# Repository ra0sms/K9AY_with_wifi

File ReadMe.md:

# K9AY receiving loop with Wi-Fi control

A remote switch for the K9AY receiving loop antenna. It is controlled over Wi-Fi from any web browser on a phone, tablet or PC. You can also control it from scripts and logging software through a simple HTTP API.

## Features

* **8 directions**: two loops switched by relays (N, NE, E, SE, S, SW, W, NW)
* **Switchable termination resistor (Rload)**: 300, 390, 430, 470, 510 or 560 Ohm
* **Built-in preamplifier**: +15 dB, switched on and off from the web page
* **ESP8266** controller (ESP-12 module with external Wi-Fi antenna)
* **Wi-Fi access point and client at the same time**: connect directly to the box, or through your home Wi-Fi network
* **Single power supply**: 12–13.8 V DC
* **Remembers its state**: direction, Rload and preamp are restored after a power loss
* **Custom direction names**: e.g. azimuth, "EU", "JA"
* **HTTP/JSON API** for automation
* Open hardware (KiCad) and open source firmware (Arduino IDE)

More information about the loop and construction details: https://ra0sms.com/k9ay-wifi-interface/

## Hardware

| Parameter | Value |
|---|---|
| Supply voltage | 12–13.8 V DC (power supply rated at least 500 mA) |
| Current consumption | about 250 mA |
| Loop connection | screw terminals **N S E W** |
| Radials / ground | screw terminal **GROUND** |
| Wi-Fi range | up to 50 m with an entry-level router |
| Case | 170 × 120 × 55 mm, ABS, IP68, cable glands for 3–7 mm cable |

* [Latest schematic (PDF)](KiCad/K9AY_switch/K9AY_switch.pdf)
* KiCad project, Gerbers and interactive BOM: [KiCad/K9AY_switch](KiCad/K9AY_switch/)

## Quick start

1. Power on the box. It creates a Wi-Fi access point:
   * Network name: **`K9AY_Loop_XXXXXX`**, where `XXXXXX` is the unique chip ID of the controller (it is also printed to the serial port at startup)
   * Password: **`1234567890`**
2. Connect your phone or PC to this network. Most devices open the controller page automatically (captive portal). If yours does not, open **http://192.168.4.1** in a browser.
3. To use the box through your home network, open **WiFi Configuration**. Pick your network from the list (click a row to fill in the name), enter the password and press **Connect**. Your router must have DHCP enabled.
4. Once it is connected, the green LED is on and the WLAN IP address is shown on the WiFi page. From any device in your home network, open the controller at:
   * **http://k9ay.local** (mDNS: Windows 10+, macOS, iOS, Linux; Android support depends on the browser), or
   * the IP address shown on the WiFi page (it can also be found in the router's DHCP list).

By default the access point stays on all the time, so you can always reach the box at `192.168.4.1`, even if the home network is down. It can also be disabled while the box is connected to your home network (see below).

## Web interface

| Page | Address | Description |
|---|---|---|
| Home | `/` | Connection info, uptime, firmware version, links to other pages |
| Direction Control | `/switch` | Main control page |
| WiFi Configuration | `/wifi` | Access point and WLAN status, network scan, connect to a router |
| Direction Labels | `/labels` | Rename the direction buttons |

### Direction Control

* The direction buttons are laid out as a compass rose. The selected direction is highlighted and also shown in the centre.
* **Rload**: selects the termination resistor of the loop.
* **PREAMP ON / OFF**: switches the +15 dB preamplifier.
* **TURN ALL OFF**: releases all relays, disconnects Rload and switches off the preamp.
* The status line at the top shows the current state, e.g. `NE 470 Ohm +15dB`. The page refreshes every 2 seconds, so changes made from another device or through the API appear by themselves. If the controller cannot be reached, the status line turns red.

### WiFi Configuration

* Name, status and IP address of the built-in access point
* **Disable access point while connected to WLAN**: the access point is turned off 30 seconds after the box connects to your home network. It turns back on automatically if the saved network is unavailable for 15 seconds, and it is always on after power-on until the WLAN connection is up. If you lose access, simply power-cycle the box and connect to `K9AY_Loop_XXXXXX`.
* Saved WLAN network, connection status, IP address, signal level and connection time
* List of available networks, sorted by signal level (press **Scan** to refresh)
* To make the box forget the saved network, submit the form with an empty SSID
* SSID up to 32 characters, password up to 64 characters

If the router cannot be reached (wrong password, router off), the controller retries every 60 seconds. The access point is active in the meantime.

### Direction Labels

Each of the 8 directions can be given its own name, up to 23 bytes. Cyrillic and other UTF-8 characters are supported. An empty field restores the default name. **Reset to defaults** restores all names at once.

## LED

| LED | Meaning |
|---|---|
| On | Connected to the home Wi-Fi network |
| Off | Not connected to WLAN (access point only) |

## HTTP API

The box can be controlled from scripts, logging software or home automation.

**Read state**

```
GET /api/state
```
```json
{"dir":1,"r":470,"pa":true,"labels":["N","NE","E","SE","S","SW","W","NW"]}
```

* `dir`: index into `labels` (0 = N, 1 = NE … 7 = NW), `-1` means off
* `r`: Rload in Ohm, `0` means off
* `pa`: preamp state

**Change state** (`POST`, form-encoded; parameters can be combined)

| Parameter | Values |
|---|---|
| `dir` | `N`, `NE`, `E`, `SE`, `S`, `SW`, `W`, `NW` |
| `r` | `300`, `390`, `430`, `470`, `510`, `560` |
| `pa` | `1` = on, `0` = off |
| `off` | `1` = turn everything off |

The response is the new state in the same format as `/api/state`. An invalid value returns HTTP 400.

```sh
curl -d "dir=NE&r=470&pa=1" http://k9ay.local/set
curl -d "off=1" http://k9ay.local/set
curl http://k9ay.local/api/state
```

**Other endpoints**

* `GET /api/info`: network status and uptime
* `GET /api/scan`: Wi-Fi scan results (`{"scanning":true}` while the scan is running)

## Firmware

Source: [src/Arduino/sketch_k9ay/sketch_k9ay.ino](src/Arduino/sketch_k9ay/sketch_k9ay.ino)

### Building

1. Install the [ESP8266 Arduino core](https://github.com/esp8266/Arduino) (tested with 3.1.2). No extra libraries are needed.
2. Board: **Generic ESP8266 Module**, Flash Size **4MB**.
3. Upload through a USB-UART adapter (GPIO0 to GND while resetting).

### Settings in the source code

At the top of the sketch:

| Constant | Default | Description |
|---|---|---|
| `softAP_password` | `1234567890` | Access point password (at least 8 characters) |
| `myHostname` | `k9ay` | mDNS name (`http://k9ay.local`) |
| `www_user` / `www_pass` | empty | Login for the web interface and API. If `www_user` is empty, no login is required |

### Stored data

The settings are stored in the emulated EEPROM, starting at address 128: Wi-Fi credentials, direction labels and the current switch state. The state is written 30 seconds after the last change, and only if it differs from the saved one. This keeps flash wear low. On the first start after an update from the old firmware, the Wi-Fi credentials saved by the old version are moved over automatically.

### Pinout

| ESP8266 | Function |
|---|---|
| GPIO13 / GPIO14 | 74HC595 data / clock (HSPI) |
| GPIO15 | 74HC595 latch |
| GPIO12 | 74HC595 output enable |
| GPIO4 | Preamp on/off |
| GPIO5 | Status LED |

Two chained 74HC595 shift registers drive the relays. The first one drives Rload (bits 0–5), the second one the direction relays.

## Documentation

* [Manual (EN)](docs/Manual_K9AY_en.pdf)
* [Manual (RU)](docs/Manual_K9AY_ru.pdf)

## License

MIT, see [LICENSE](LICENSE). © 2022 Anton Gavrilov RA0SMS

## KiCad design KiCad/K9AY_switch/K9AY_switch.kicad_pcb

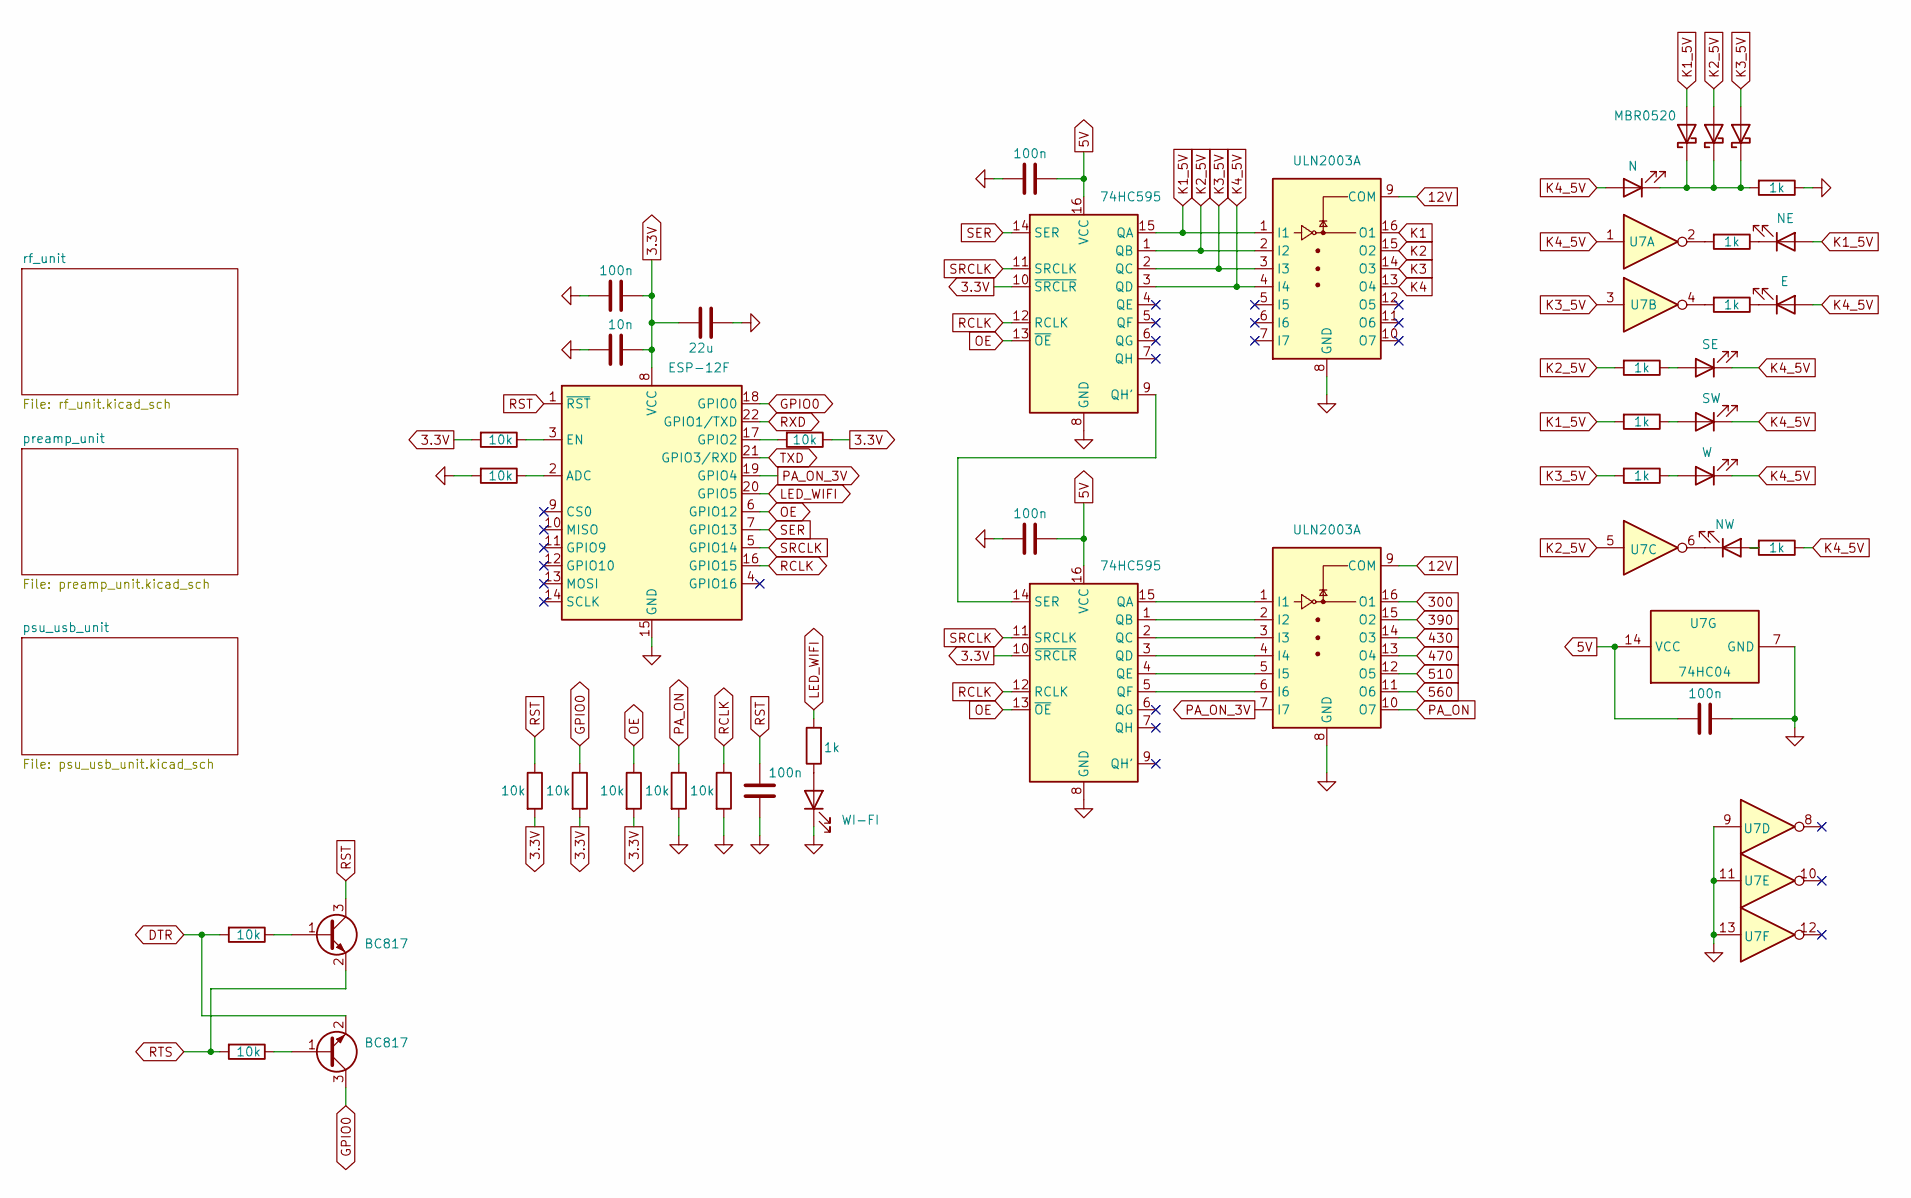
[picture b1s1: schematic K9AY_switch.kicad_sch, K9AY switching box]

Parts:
C6, C16, C17, C18, C19: 100n; C_1206_3216Metric
C14: 10n; C_1206_3216Metric
C15: 22u; C_1206_3216Metric
D4: WI-FI; LED_1206_3216Metric
D5: N; LED_1206_3216Metric
D6, D7, D8: MBR0520; D_SOD-123
D9: NE; LED_1206_3216Metric
D10: E; LED_1206_3216Metric
D11: SE; LED_1206_3216Metric
D12: SW; LED_1206_3216Metric
D13: W; LED_1206_3216Metric
D14: NW; LED_1206_3216Metric
Q2, Q3: BC817; SOT-23
R7, R12, R13, R14, R15, R16, R17, R18, R20, R21: 10k; R_1206_3216Metric
R19, R22, R23, R24, R25, R26, R27, R28: 1k; R_1206_3216Metric
U1: ESP-12F; ESP-12E
U2, U3: 74HC595; SOIC-16_3.9x9.9mm_P1.27mm
U4, U8: ULN2003A; SOIC-16_3.9x9.9mm_P1.27mm
U7: 74HC04; SOIC-14_3.9x8.7mm_P1.27mm

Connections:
3.3V: C6.2, C14.2, C15.2, R12.2, R14.2, R15.2, R16.1, R20.2, U1.8 (VCC), U2.10 (~SRCLR), U3.10 (~SRCLR); also elsewhere on the board
5V: C17.2, C18.2, C19.1, U2.16 (VCC), U3.16 (VCC), U7.14 (VCC); also elsewhere on the board
12V: U4.9 (COM), U8.9 (COM); also elsewhere on the board
300: U8.16 (O1); also elsewhere on the board
390: U8.15 (O2); also elsewhere on the board
430: U8.14 (O3); also elsewhere on the board
470: U8.13 (O4); also elsewhere on the board
510: U8.12 (O5); also elsewhere on the board
560: U8.11 (O6); also elsewhere on the board
DTR: Q3.2 (E), R18.2; also elsewhere on the board
GND: C6.1, C14.1, C15.1, C16.1, C17.1, C18.1, C19.2, D4.1 (K), R7.2, R13.2, R21.2, R22.1, U1.15 (GND), U2.8 (GND), U3.8 (GND), U4.8 (GND), U7.7 (GND), U7.9, U7.11, U7.13, U8.8 (GND); also elsewhere on the board
GPIO0: Q3.3 (C), R15.1, U1.18 (GPIO0)
K1: U4.16 (O1); also elsewhere on the board
K1_5V: D6.2 (A), D9.2 (A), R26.2, U2.15 (QA), U4.1 (I1)
K2: U4.15 (O2); also elsewhere on the board
K2_5V: D7.2 (A), R25.2, U2.1 (QB), U4.2 (I2), U7.5
K3: U4.14 (O3); also elsewhere on the board
K3_5V: D8.2 (A), R27.2, U2.2 (QC), U4.3 (I3), U7.3
K4: U4.13 (O4); also elsewhere on the board
K4_5V: D5.2 (A), D10.2 (A), D11.1 (K), D12.1 (K), D13.1 (K), R28.1, U2.3 (QD), U4.4 (I4), U7.1
LED_WIFI: R19.2, U1.20 (GPIO5)
unnamed: D4.2 (A), R19.1
unnamed: D5.1 (K), D6.1 (K), D7.1 (K), D8.1 (K), R22.2
unnamed: D9.1 (K), R23.1
unnamed: D10.1 (K), R24.1
unnamed: D11.2 (A), R25.1
unnamed: D12.2 (A), R26.1
unnamed: D13.2 (A), R27.1
unnamed: D14.2 (A), R28.2
unnamed: D14.1 (K), U7.6
unnamed: Q2.1 (B), R18.1
unnamed: Q3.1 (B), R17.1
unnamed: R23.2, U7.2
unnamed: R24.2, U7.4
unnamed: R13.1, U1.2 (ADC)
unnamed: R12.1, U1.3 (EN)
unnamed: R16.2, U1.17 (GPIO2)
unnamed: U2.9 (QH'), U3.14 (SER)
unnamed: U3.15 (QA), U8.1 (I1)
unnamed: U3.1 (QB), U8.2 (I2)
unnamed: U3.2 (QC), U8.3 (I3)
unnamed: U3.3 (QD), U8.4 (I4)
unnamed: U3.4 (QE), U8.5 (I5)
unnamed: U3.5 (QF), U8.6 (I6)
OE: R20.1, U1.6 (GPIO12), U2.13 (~OE), U3.13 (~OE)
PA_ON: R21.1, U8.10 (O7); also elsewhere on the board
PA_ON_3V: U1.19 (GPIO4), U8.7 (I7)
RCLK: R7.1, U1.16 (GPIO15), U2.12 (RCLK), U3.12 (RCLK)
RST: C16.2, Q2.3 (C), R14.1, U1.1 (~RST)
RTS: Q2.2 (E), R17.2; also elsewhere on the board
RXD: U1.22 (GPIO1/TXD); also elsewhere on the board
SER: U1.7 (GPIO13), U2.14 (SER)
SRCLK: U1.5 (GPIO14), U2.11 (SRCLK), U3.11 (SRCLK)
TXD: U1.21 (GPIO3/RXD); also elsewhere on the board

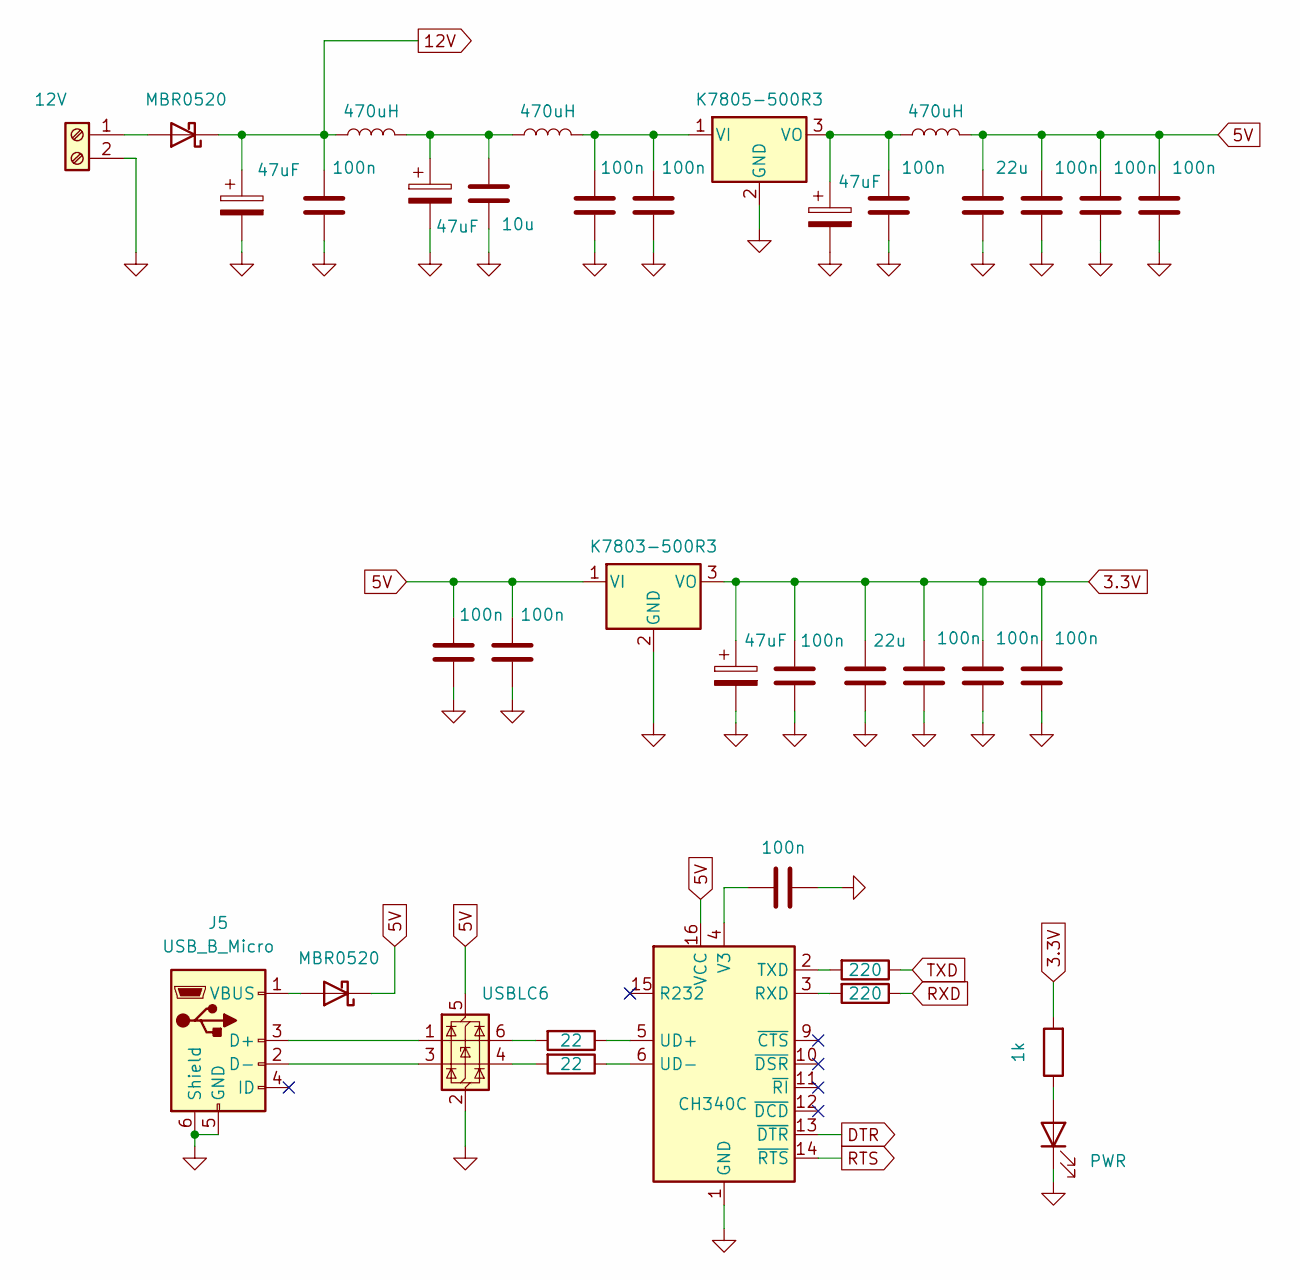
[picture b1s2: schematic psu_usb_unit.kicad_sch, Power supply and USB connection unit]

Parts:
C1, C7, C10, C30: 47uF; CP_Radial_D5.0mm_P2.50mm
C2, C8, C11, C13, C22, C23, C24, C25, C26, C27, C28, C29, C35, C36: 100n; C_1206_3216Metric
C9, C12: 22u; C_1206_3216Metric
C32: 10u; C_1206_3216Metric
D1, D3: MBR0520; D_SOD-123
D2: PWR; LED_1206_3216Metric
J4: 12V; TerminalBlock_MetzConnect_Type011_RT05502HBWC_1x02_P5.00mm_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
J5: USB_B_Micro; USB_Mini-B_Wuerth_65100516121_Horizontal
L2, L3, L4: 470uH; L_Radial_D10.0mm_P5.00mm_Neosid_SD12_style3
R1: 1k; R_1206_3216Metric
R8, R9: 22; R_1206_3216Metric
R10, R11: 220; R_1206_3216Metric
U5: K7803-500R3; TO-220-3_Vertical
U6: K7805-500R3; TO-220-3_Vertical
U11: CH340C; SOIC-16_3.9x9.9mm_P1.27mm
U12: USBLC6; SOT-23-6

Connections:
3.3V: C7.1, C8.1, C9.1, C27.1, C28.1, C29.1, R1.2, U5.3 (VO); also elsewhere on the board
5V: C12.1, C24.1, C25.1, C26.1, C35.1, C36.1, D3.1 (K), L4.2, U5.1 (VI), U11.16 (VCC), U12.5 (VBUS); also elsewhere on the board
12V: C1.1, C2.1, D1.1 (K), L3.1; also elsewhere on the board
DTR: U11.13 (~DTR); also elsewhere on the board
GND: C1.2, C2.2, C7.2, C8.2, C9.2, C10.2, C11.2, C12.2, C13.2, C22.2, C23.2, C24.2, C25.2, C26.2, C27.2, C28.2, C29.2, C30.2, C32.2, C35.2, C36.2, D2.1 (K), J4.2, J5.5 (GND), J5.6 (Shield), U5.2 (GND), U6.2 (GND), U11.1 (GND), U12.2 (GND); also elsewhere on the board
unnamed: C30.1, C32.1, L2.1, L3.2
unnamed: D1.2 (A), J4.1
unnamed: D2.2 (A), R1.1
unnamed: D3.2 (A), J5.1 (VBUS)
unnamed: J5.3 (D+), U12.1 (I/O1)
unnamed: J5.2 (D-), U12.3 (I/O2)
unnamed: R8.2, U12.4 (I/O2)
unnamed: R9.2, U12.6 (I/O1)
unnamed: C22.1, C23.1, L2.2, U6.1 (VI)
unnamed: C10.1, C11.1, L4.1, U6.3 (VO)
unnamed: R11.2, U11.3 (RXD)
unnamed: R10.2, U11.2 (TXD)
unnamed: R9.1, U11.5 (UD+)
unnamed: R8.1, U11.6 (UD-)
unnamed: C13.1, U11.4 (V3)
RTS: U11.14 (~RTS); also elsewhere on the board
RXD: R11.1; also elsewhere on the board
TXD: R10.1; also elsewhere on the board

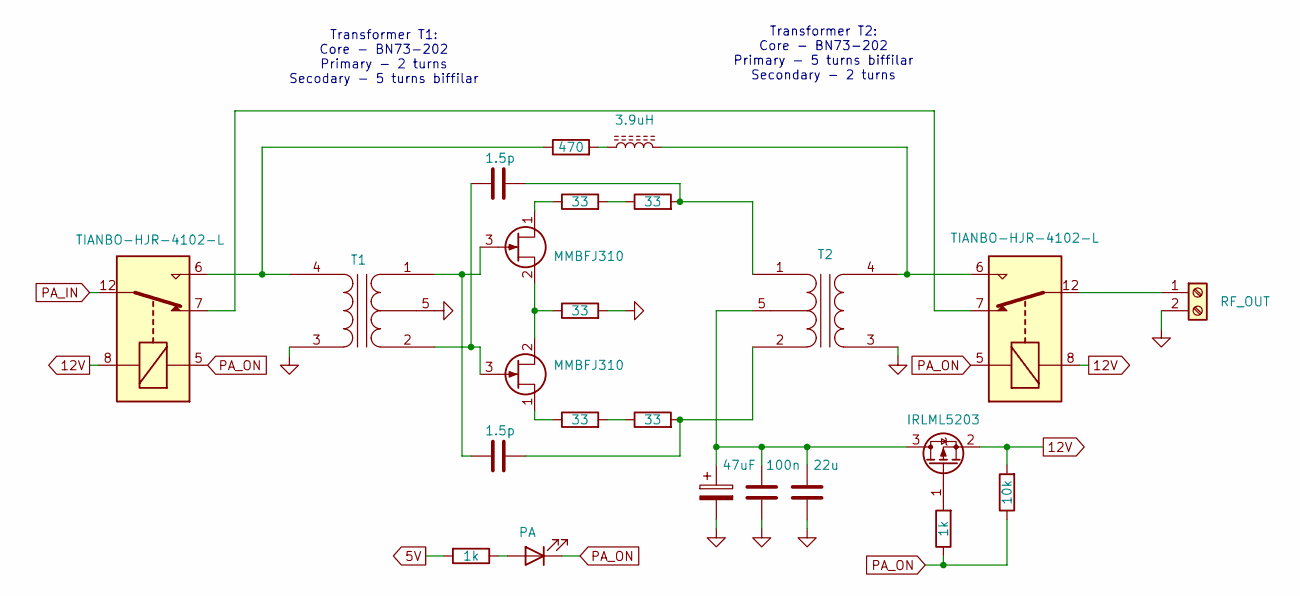
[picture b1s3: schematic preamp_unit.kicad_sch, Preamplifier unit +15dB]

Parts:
C3, C5: 1.5p; C_1206_3216Metric
C4: 47uF; CP_Radial_D5.0mm_P2.50mm
C20: 100n; C_1206_3216Metric
C21: 22u; C_1206_3216Metric
D15: PA; LED_1206_3216Metric
J6: RF_OUT; PinSocket_1x02_P2.54mm_Vertical
K11, K12: TIANBO-HJR-4102-L; Relay_SPDT_HJR-4102
L1: 3.9uH; L_1206_3216Metric
Q1, Q4: MMBFJ310; SOT-23
Q5: IRLML5203; SOT-23
R3, R4, R5, R29, R30: 33; R_1206_3216Metric
R35: 470; R_1206_3216Metric
R36: 10k; R_1206_3216Metric
R37, R38: 1k; R_1206_3216Metric
T1, T2: Transformer_J310

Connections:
5V: R38.2; also elsewhere on the board
12V: K11.8, K12.8, Q5.2 (S), R36.2; also elsewhere on the board
GND: C4.2, C20.2, C21.2, J6.2, R5.2, T1.3 (SA), T1.5, T2.3 (SA); also elsewhere on the board
unnamed: D15.2 (A), R38.1
unnamed: J6.1, K12.12
unnamed: K11.7, K12.7
unnamed: L1.1, R35.2
unnamed: Q1.1 (D), R29.1
unnamed: C3.1, Q1.3 (G), T1.1 (AA)
unnamed: Q1.2 (S), Q4.2 (S), R5.1
unnamed: Q4.1 (D), R3.1
unnamed: C5.1, Q4.3 (G), T1.2 (AB)
unnamed: C4.1, C20.1, C21.1, Q5.3 (D), T2.5
unnamed: Q5.1 (G), R37.2
unnamed: R3.2, R4.1
unnamed: R29.2, R30.1
unnamed: K11.6, R35.1, T1.4 (SB)
unnamed: C5.2, R30.2, T2.1 (AA)
unnamed: C3.2, R4.2, T2.2 (AB)
unnamed: K12.6, L1.2, T2.4 (SB)
PA_IN: K11.12; also elsewhere on the board
PA_ON: D15.1 (K), K11.5, K12.5, R36.1, R37.1; also elsewhere on the board

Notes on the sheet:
Transformer T1: Core - BN73-202 Primary - 2 turns Secodary - 5 turns biffilar
Transformer T2: Core - BN73-202 Primary - 5 turns biffilar Secondary - 2 turns

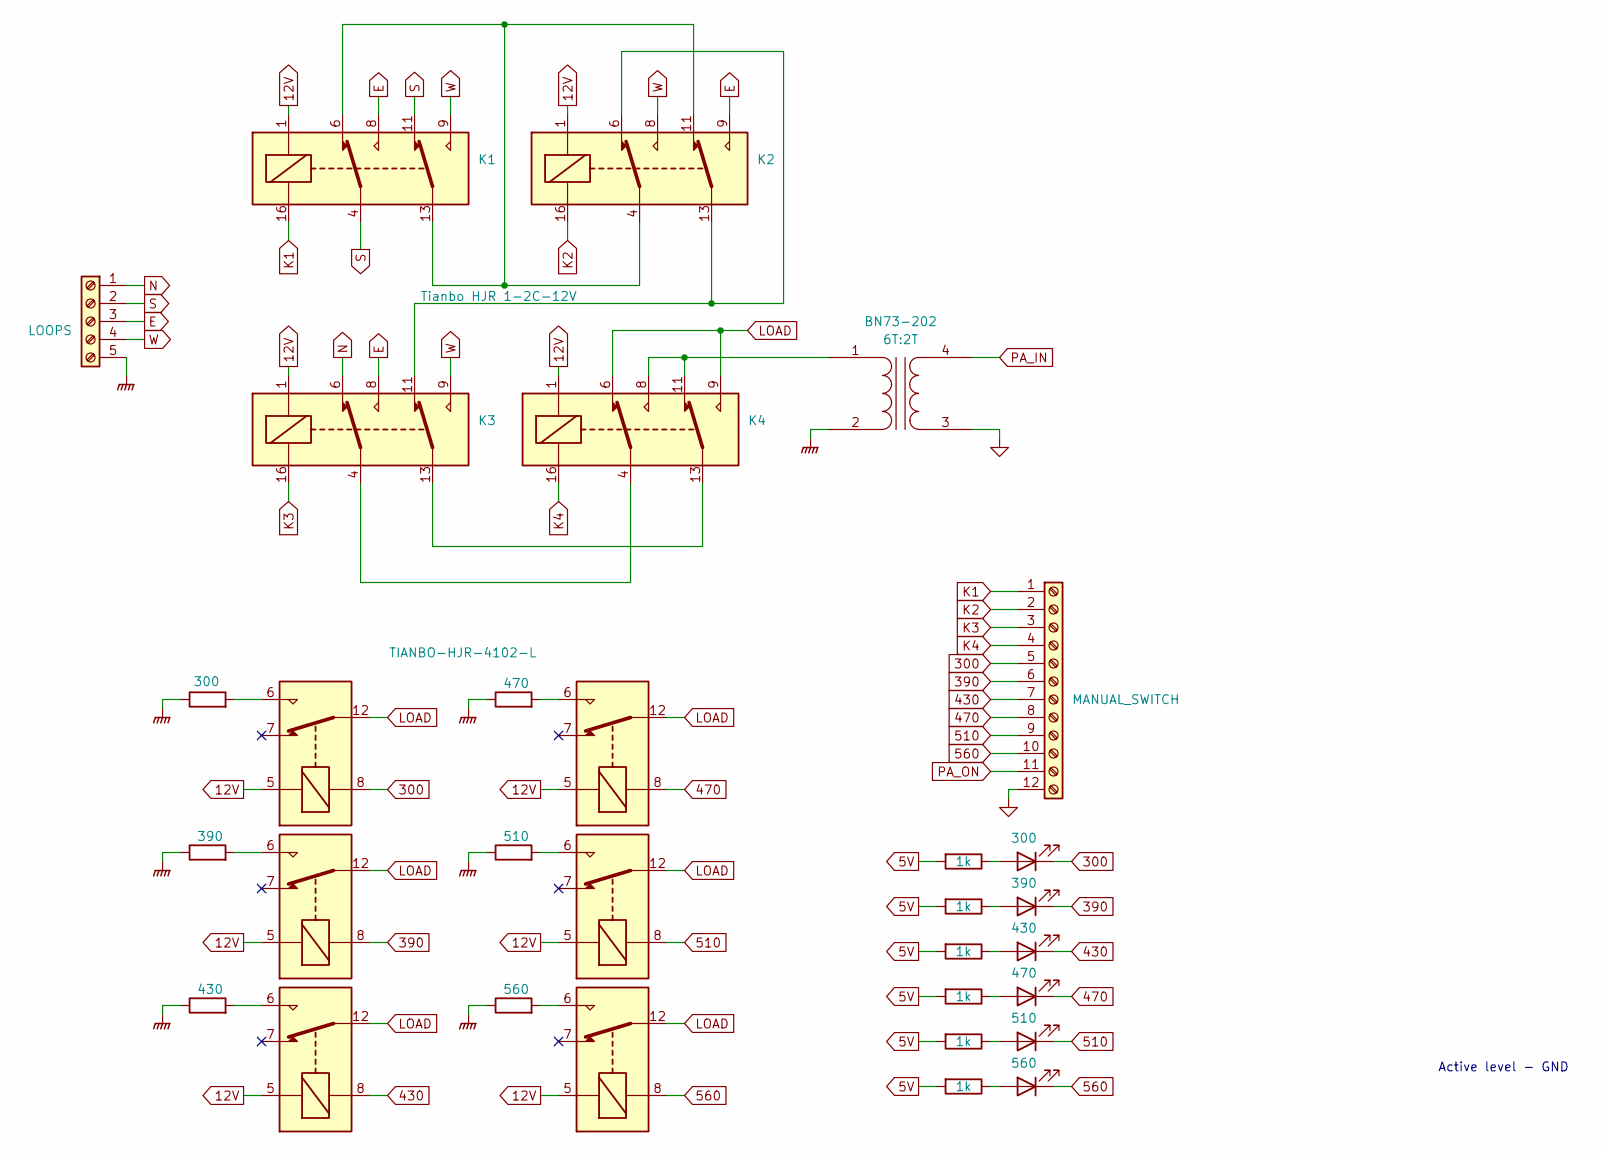
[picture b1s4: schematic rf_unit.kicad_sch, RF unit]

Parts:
BN73-202: 6T:2T; Transformer_BN73-202
D16: 300; LED_1206_3216Metric
D17: 390; LED_1206_3216Metric
D18: 430; LED_1206_3216Metric
D19: 470; LED_1206_3216Metric
D20: 510; LED_1206_3216Metric
D21: 560; LED_1206_3216Metric
J3: LOOPS; TerminalBlock_MetzConnect_Type011_RT05505HBWC_1x05_P5.00mm_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
J7: MANUAL_SWITCH; TerminalBlock_MaiXu_MX126-5.0-12P_1x12_P5.00mm
K1, K2, K4: G5V-2; Relay_DPDT_Omron_G5V-2
K3: Tianbo HJR 1-2C-12V; Relay_DPDT_Omron_G5V-2
K5, K6, K7, K8, K9, K10: TIANBO-HJR-4102-L; Relay_SPDT_HJR-4102
R2: 300; R_2512_6332Metric_Pad1.40x3.35mm_HandSolder
R6: 390; R_2512_6332Metric_Pad1.40x3.35mm_HandSolder
R31: 430; R_2512_6332Metric_Pad1.40x3.35mm_HandSolder
R32: 470; R_2512_6332Metric_Pad1.40x3.35mm_HandSolder
R33: 510; R_2512_6332Metric_Pad1.40x3.35mm_HandSolder
R34: 560; R_2512_6332Metric_Pad1.40x3.35mm_HandSolder
R39, R40, R41, R42, R43, R44: 1k; R_1206_3216Metric

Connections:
5V: R39.2, R40.2, R41.2, R42.2, R43.2, R44.2; also elsewhere on the board
12V: K1.1, K2.1, K3.1, K4.1, K5.5, K6.5, K7.5, K8.5, K9.5, K10.5; also elsewhere on the board
300: D16.1 (K), J7.5, K5.8; also elsewhere on the board
390: D17.1 (K), J7.6, K6.8; also elsewhere on the board
430: D18.1 (K), J7.7, K7.8; also elsewhere on the board
470: D19.1 (K), J7.8, K8.8; also elsewhere on the board
510: D20.1 (K), J7.9, K9.8; also elsewhere on the board
560: D21.1 (K), J7.10, K10.8; also elsewhere on the board
E: J3.3, K1.8, K2.9, K3.8
GND: BN73-202.3 (SA), J7.12; also elsewhere on the board
GNDPWR: BN73-202.2 (AB), J3.5, R2.1, R6.1, R31.1, R32.1, R33.1, R34.1
K1: J7.1, K1.16; also elsewhere on the board
K2: J7.2, K2.16; also elsewhere on the board
K3: J7.3, K3.16; also elsewhere on the board
K4: J7.4, K4.16; also elsewhere on the board
LOAD: K4.6, K4.9, K5.12, K6.12, K7.12, K8.12, K9.12, K10.12
N: J3.1, K3.6
unnamed: BN73-202.1 (AA), K4.8, K4.11
unnamed: D16.2 (A), R39.1
unnamed: D17.2 (A), R40.1
unnamed: D18.2 (A), R41.1
unnamed: D19.2 (A), R42.1
unnamed: D20.2 (A), R43.1
unnamed: D21.2 (A), R44.1
unnamed: K1.6, K1.13, K2.4, K2.11
unnamed: K2.6, K2.13, K3.11
unnamed: K3.4, K4.4
unnamed: K3.13, K4.13
unnamed: K5.6, R2.2
unnamed: K6.6, R6.2
unnamed: K7.6, R31.2
unnamed: K8.6, R32.2
unnamed: K9.6, R33.2
unnamed: K10.6, R34.2
PA_IN: BN73-202.4 (SB); also elsewhere on the board
PA_ON: J7.11; also elsewhere on the board
S: J3.2, K1.4, K1.11
W: J3.4, K1.9, K2.8, K3.9

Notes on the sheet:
Active level - GND

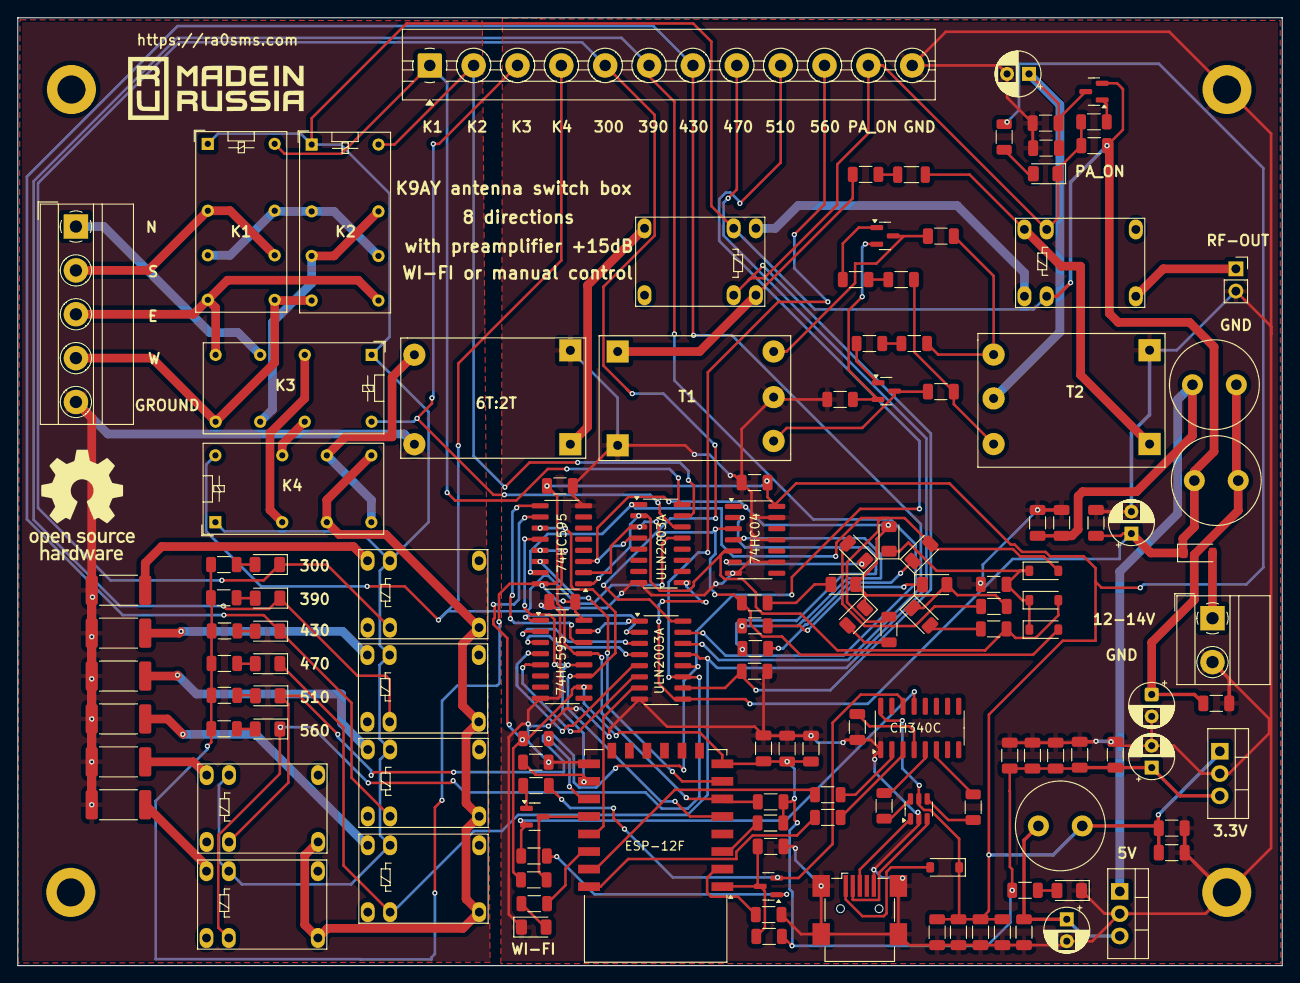
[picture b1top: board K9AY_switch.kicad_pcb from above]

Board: 2 copper layers, 144.1 x 108.1 mm, 137 parts (0 on the bottom side), 110 nets.

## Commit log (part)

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2022-12-02 1st commit
2022-12-03 added Readme.md
2022-12-03 Create LICENSE
2023-01-01 add pics, modified src
2023-01-01 add manual and some pics
2023-02-22 corrected SPI init
2023-07-06 Added English manual
2024-04-01 correct manual
2025-03-12 fix some issues
2025-03-23 add revision 2 in KiCad
2025-03-23 change pics
2025-05-27 change web interface
2025-05-27 add pics
